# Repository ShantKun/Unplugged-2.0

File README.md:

Smart City Sentinel - Modular PCB for Intelligent Environmental Monitoring

⸻

Project Overview

The Smart City Sentinel is a modular PCB designed for intelligent environmental monitoring in urban spaces. This project integrates multiple sensors, power management systems, and real-time data transmission capabilities within a scalable architecture. The design follows strict connectivity and power constraints, ensuring stability, reliability, and modular expansion for future enhancements.

⸻

Features
	•	Modular PCB design with sensor interfacing for real-time environmental monitoring.
	•	Integrated buck-boost converter for stable voltage regulation.
	•	Fujitsu Relay implemented as a kill switch to protect components from potential damage.
	•	Efficient power management with battery monitoring and solar panel interface.
	•	Compliance with Electrical Rule Check (ERC) and Design Rule Check (DRC) standards.
	•	Compact 3D CAD model ensuring structural compatibility with the predefined solar panel.

⸻

Hardware Components

Component	Description
ESP32-S3-WROOM-1-N16R8	Main microcontroller for data processing and wireless communication.
TP4056	Rechargeable module for battery charging and management.
TLV61070ADBV	Buck-boost converter for stable 3.3V output.
Fujitsu Relay (FTR-LYCA005x)	Kill switch implementation for component protection.
MAX471	Dual-signal current and voltage sensor for accurate monitoring.
OLED Display	Visual data representation interface.
RTC DS3231	Real-time clock for precise timekeeping.
MQ-135 Gas Sensor	Detects harmful gases and air quality.
DHT11	Temperature and humidity sensor.
BME280	Environmental sensor for pressure, humidity, and temperature.
IM69D130	High-performance sound sensor.
A1301KHLT-T	Hall effect sensor for magnetic field detection.
Water Flow Sensor	Monitors fluid flow rates.
Soil Moisture Sensor	Detects soil moisture levels.
Rain Sensor	Identifies rainfall presence.
IR Flame Sensor	Detects flame presence for fire monitoring.
Dust Sensor	Measures airborne particle levels.
Rechargeable Battery (3.7V 2500mAh)	Power source for continuous operation.

⸻

Setup Instructions
	1.	Assemble the PCB according to the provided schematic.
	2.	Flash the ESP32 with the provided firmware.
	3.	Ensure the battery is charged and securely connected via the TP4056 module.
	4.	Monitor data outputs on the OLED display and via the ESP32 serial monitor.
	5.	Test the Fujitsu Relay kill switch by inducing abnormal conditions (e.g., overcurrent) to confirm it safely disconnects power.

⸻

Future Improvements
	•	Implement wireless data transmission for remote monitoring.
	•	Integrate predictive maintenance algorithms to prevent component failure.
	•	Expand modularity by adding additional sensor headers.

⸻

⸻

For further guidance or technical assistance, feel free to contact the project contributors.

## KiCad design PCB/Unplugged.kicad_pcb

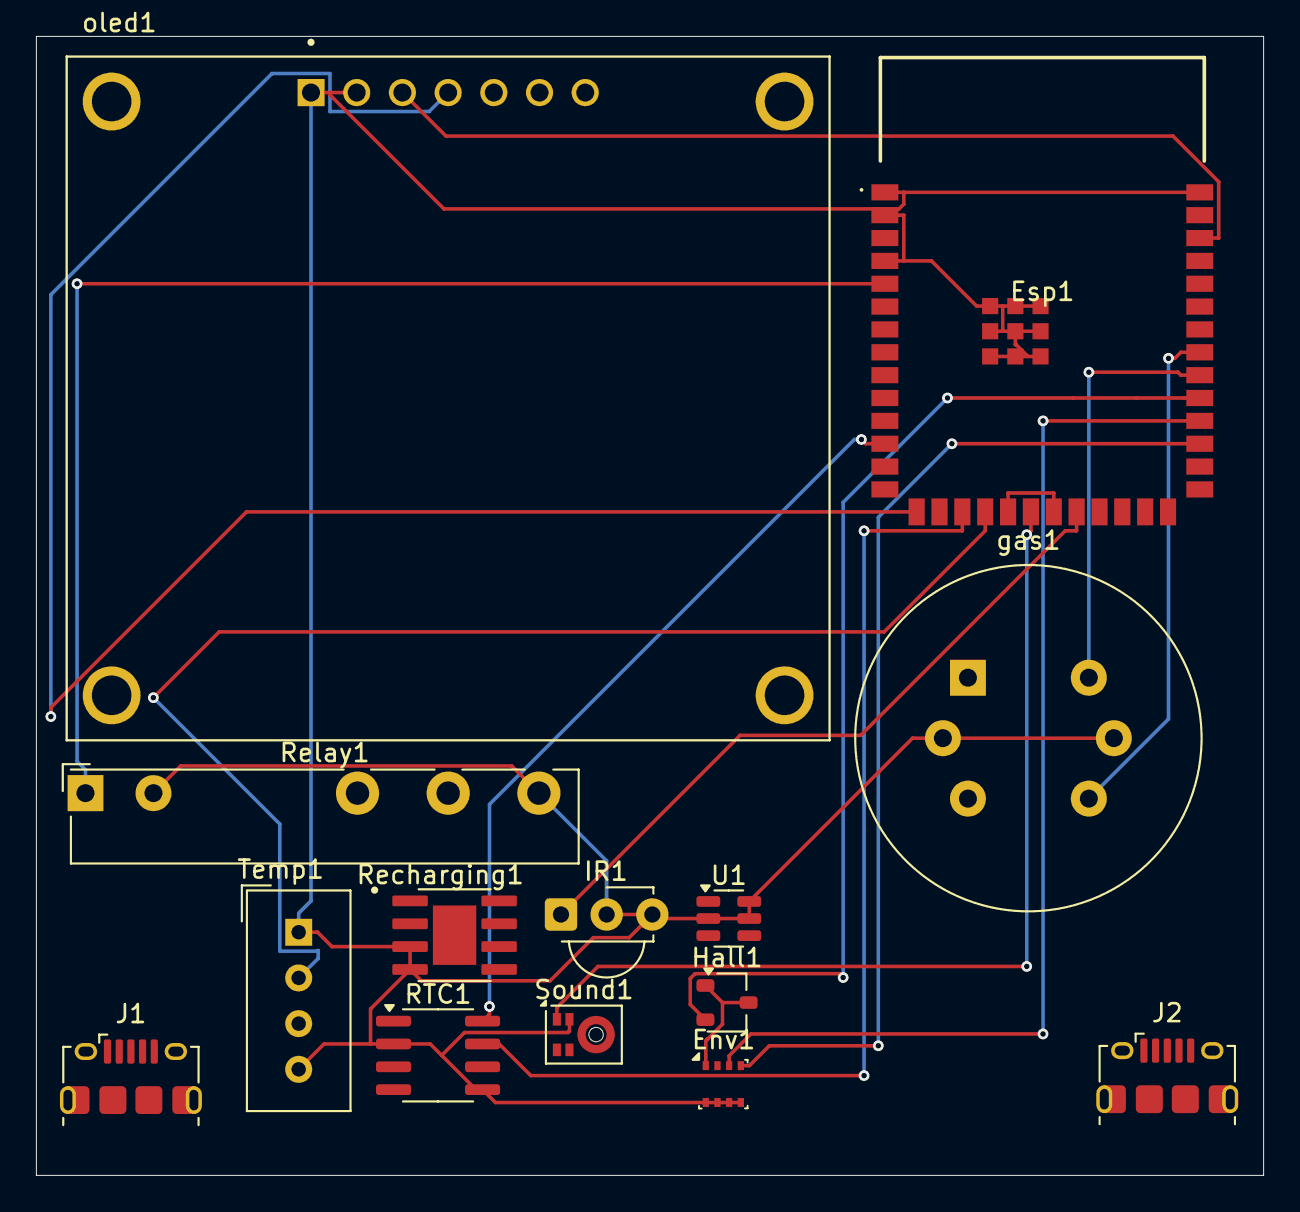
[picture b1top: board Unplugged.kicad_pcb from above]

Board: 2 copper layers, 68.2 x 63.3 mm, 14 parts (0 on the bottom side), 15 nets.

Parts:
Env1: BME280; Bosch_LGA-8_2.5x2.5mm_P0.65mm_ClockwisePinNumbering
Esp1: ESP32-S3-WROOM-1-N16R8; ESP32S3WROOM1N8R2
Hall1: A1301KLHLT-T; SOT-23W
IR1: TSSP58038; Vishay_MINICAST-3Pin
J1, J2: USB_B_Micro; USB_Micro-B_Amphenol_10118194_Horizontal
RTC1: DS3231MZ; SOIC-8_3.9x4.9mm_P1.27mm
Recharging1: TP4056; SOP127P600X175-9N
Relay1: Fujitsu_FTR-LYCA005x; Relay_SPDT_Fujitsu_FTR-LYCA005x_FormC_Vertical
Sound1: IM69D130; Infineon_PG-LLGA-5-1
Temp1: DHT11; Aosong_DHT11_5.5x12.0_P2.54mm
U1: TLV61070ADBV; SOT-23-6
gas1: MQ-6
oled1: AOM12864A0-1.54WW-ANO; LCD_AOM12864A0-1.54WW-ANO

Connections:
+3V8: Env1.1 (GND), Env1.5 (SDO), Env1.6 (VDDIO), Env1.7 (GND), Env1.8 (VDD), Esp1.1 (GND), Esp1.2 (3V3), Esp1.4 (IO4), Esp1.40 (GND), Esp1.41 (GND), Esp1.42 (GND), Esp1.43 (GND), Esp1.44 (GND), Esp1.45 (GND), Esp1.46 (GND), Esp1.47 (GND), Esp1.48 (GND), Esp1.49 (GND), Hall1.1 (VCC), Hall1.3 (GND), IR1.2 (GND), IR1.3 (Vs), RTC1.2 (VCC), RTC1.5 (GND), Recharging1.3 (GND), Recharging1.4 (VCC), Relay1.14, Relay1.A2, Sound1.2 (VDD), Sound1.5 (GND), Temp1.1 (VDD), Temp1.4 (GND), U1.2 (GND), U1.5 (V_{OUT}), U1.6 (V_{IN}), gas1.2 (VH+), gas1.5 (VH-), oled1.1 (GND), oled1.2 (VDD)
/IO2: Esp1.38 (IO2), oled1.3 (SCL)
/IO3: Esp1.15 (IO3), oled1.4 (SDA)
/IO5: Esp1.5 (IO5), Relay1.A1
/IO8: Esp1.12 (IO8), RTC1.8 (SCL)
/IO9: Esp1.17 (IO9), RTC1.7 (SDA)
/IO10: Esp1.18 (IO10), Temp1.2 (DATA)
/IO11: Esp1.19 (IO11), Esp1.21 (IO13)
/IO20: Esp1.20 (IO12), Sound1.1 (DATA)
/IO36: Env1.4 (SCK), Esp1.29 (IO36)
/IO37: Env1.3 (SDI), Esp1.30 (IO37)
/IO38: Esp1.31 (IO38), Esp1.35 (IO42), Hall1.2 (VOUT)
/IO39: Esp1.32 (IO39), gas1.6 (A1)
/IO40: Esp1.33 (IO40), gas1.4 (A2)
unnamed: Esp1.22 (IO14), IR1.1 (OUT)

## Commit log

2025-03-08 Create a
